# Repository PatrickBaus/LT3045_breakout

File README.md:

LT3042/LT3045 Breakout Board
===================

This repository contains the KiCAD PCB project files for a breakout board for the Linear Technologies LT3042/LT3045  ultralow noise, ultrahigh PSRR, 200/500 mA LDO regulator (http://www.linear.com/product/LT3042, http://www.linear.com/product/LT3045).

About
-----
This breakout board supports both the LT3042 and LT3045 LDO regulator. The package is designed as a drop-in replacement for the popular 78xx series.

The root folder contains the KiCAD files and the bill of materials, while the gerber files can be found in the [/gerber](gerber/) folder.

Thermal considerations
-----
The breakout board was tested with an LT3045 with different heat sink configurations to give an estimate on the expected temperature rise. This should help with the decision whether to add a heat sink or not. The test was done using a 35 µm (1 oz./ft²) copper board. The LT3045 was configured for an 11 V output from a 13 V input running at ~500 mA.

Using a thermal imaging camera the temperature was measured and the thermal resistance was calculated using the known ambient temperature (~23 °C).

##### No Heat Sink

##### Using a 25 K/W Heat Sink

Dropping 2 V @ 500 mA, a Fischer Elekronik [FK 220 SA 220](http://www.fischerelektronik.de/web_fischer/en_GB/heatsinks/C02/Attachable%20heatsink/PR/FK220_SA_220_/datasheet.xhtml) heat sink was used without any thermal compound. Because of the mounting style of the pin header (contacts on the back side of the board) some slight modification of the heat sink is required. A small cutout needs to be made using a file. If the heatsink is to be attached permanetely some thermal adhesive to glue it in place is recommended.

##### Summary Table

|Heat Sink|Power Dissipated|Thermal Resistance|
|---------|----------------|------------------|
|None     |~1 W            |~44 K/W           |
|25 K/W   |~1 W            |~22 K/W           |

I do recommend using a heat sink or bolting the LT3045 PCB down onto the main PCB when running the LT3045 @ 500 mA. Although the chip is within its design specifications, running it at more than 60 °C will shorten its live and touching it can be rather unpleasant. Any small heat sink should be sufficient at room temperature, but your milage may vary.

Related Repositories
-------------
See the following repositories for more information

KiCAD footprints: https://github.com/PatrickBaus/footprints.pretty

KiCAD 3D models: https://github.com/PatrickBaus/footprints.3dshapes

KiCAD schematic libraries: https://github.com/PatrickBaus/KiCad-libraries

License
-------

This work is released under the Cern OHL v.1.2
See www.ohwr.org/licenses/cern-ohl/v1.2 or the included LICENSE file for more information.

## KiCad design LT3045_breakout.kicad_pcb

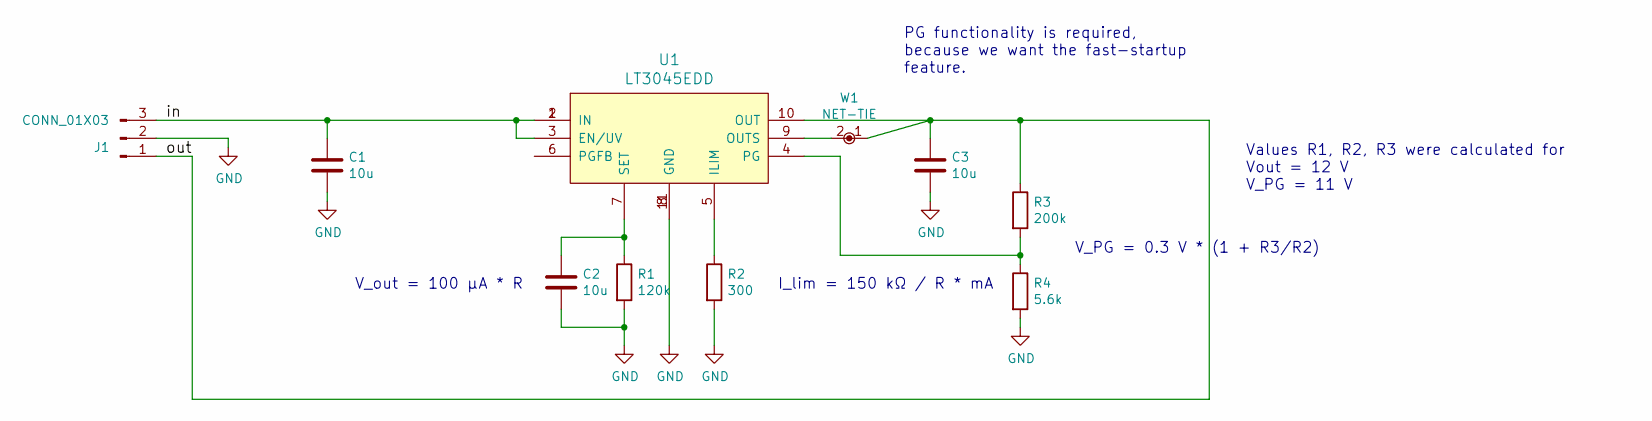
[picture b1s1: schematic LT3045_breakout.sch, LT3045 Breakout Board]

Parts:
C1, C2, C3: 10u; C_0603
J1: CONN_01X03; Pin_Header_Angled_1x03_Pitch2.54mm
R1: 120k; R_0603
R2: 300; R_0603
R3: 200k; R_0402
R4: 5.6k; R_0402
U1: LT3045EDD; DFN-10-1EP_3x3mm_Pitch0.5mm
W1: NET-TIE; NET-TIE-0.15mm

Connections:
/in: C1.1, J1.3, U1.1 (IN), U1.2 (IN), U1.3 (EN/UV)
/out: C3.1, J1.1, R3.1, U1.10 (OUT), W1.1
GND: C1.2, C2.2, C3.2, J1.2, R1.2, R2.2, R4.2, U1.8 (GND), U1.11
unnamed: C2.1, R1.1, U1.7 (SET)
unnamed: R2.1, U1.5 (ILIM)
unnamed: R3.2, R4.1, U1.4 (PG)
unnamed: U1.9 (OUTS), W1.2

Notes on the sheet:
PG functionality is required, because we want the fast-startup feature.
V_out = 100 µA * R
I_lim = 150 kΩ / R * mA
V_PG = 0.3 V * (1 + R3/R2)
Values R1, R2, R3 were calculated for Vout = 12 V V_PG = 11 V

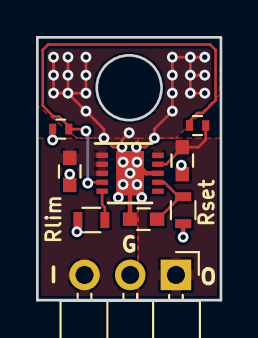
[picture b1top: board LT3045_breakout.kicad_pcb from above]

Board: 2 copper layers, 10.2 x 14.6 mm, 10 parts (0 on the bottom side), 7 nets.

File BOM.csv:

Date:,2017-12-14T22:19:19 CET,,,,,
Tool:,Eeschema (2017-06-16 revision 2018d4894)-master,,,,,
Component Count:,10,,,,,
Ref,Qnty,Value,Cmp name,Footprint,Description,Vendor
"C3, C1, C2, ",3,10u,GRM188R6YA106MA73D,Capacitors_SMD:C_0603,Unpolarized capacitor,Murata
"J1, ",1,CONN_01X03,68016-403HLF,Pin_Headers:Pin_Header_Angled_1x03_Pitch2.54mm,"Generic connector, single row, 01x03",Amphenol
"R1, ",1,120k,RR0816P-124-D,Resistors_SMD:R_0603,Resistor,Susumu
"R2, ",1,300,RR0816P-301-D,Resistors_SMD:R_0603,Resistor,Susumu
"R3, ",1,200k,MCS04020C2003FE000,Resistors_SMD:R_0402,Resistor,Vishay
"R4, ",1,5.6k,RR0510P-562-D,Resistors_SMD:R_0402,Resistor,Susumu
"U1, ",1,LT3045EDD,LT3045EDD,Housings_DFN_QFN:DFN-10-1EP_3x3mm_Pitch0.5mm,"20V, 500mA, Ultralow Noise, Ultrahigh PSRR Linear Regulator, DFN Package",Linear Technology
"W1, ",1,NET-TIE,,Custom footprints:NET-TIE-0.15mm,,

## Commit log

2017-08-08 fixed image link
2017-08-11 Added label '78xx' to the board Added .gitignore file
2017-08-12 Moved via to have a better guard ring for the setpoint
2017-08-12 Updated Gerber files
2017-08-12 Added more descriptive text to the board
2017-08-15 Removed PGFB pull resistor. We do not need that.
2017-08-15 Changed resistor values to outout 12V@500mA
2017-08-16 Added text to denote Rlim and Rset Changed 3d model of the pin header
2017-08-16 Updated picture of the board
2017-08-16 Moved GND label on front silk screen Updated gerber files
2017-12-14 Updated to v1.1 Added BOM Removed old gerber files Updated component values on the pcb board
2017-12-14 Fixed layer description
2017-12-14 Changed units from inch to metric
2017-12-14 Updated libraries
2018-04-09 Updated Readme with thermal info
2018-04-09 fixed typo
2018-04-12 Added more info on using a heat sink

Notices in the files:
LT3045_breakout.sch:
Copyright (©) 2017, Patrick Baus
Licensed under CERN OHL v.1.2
